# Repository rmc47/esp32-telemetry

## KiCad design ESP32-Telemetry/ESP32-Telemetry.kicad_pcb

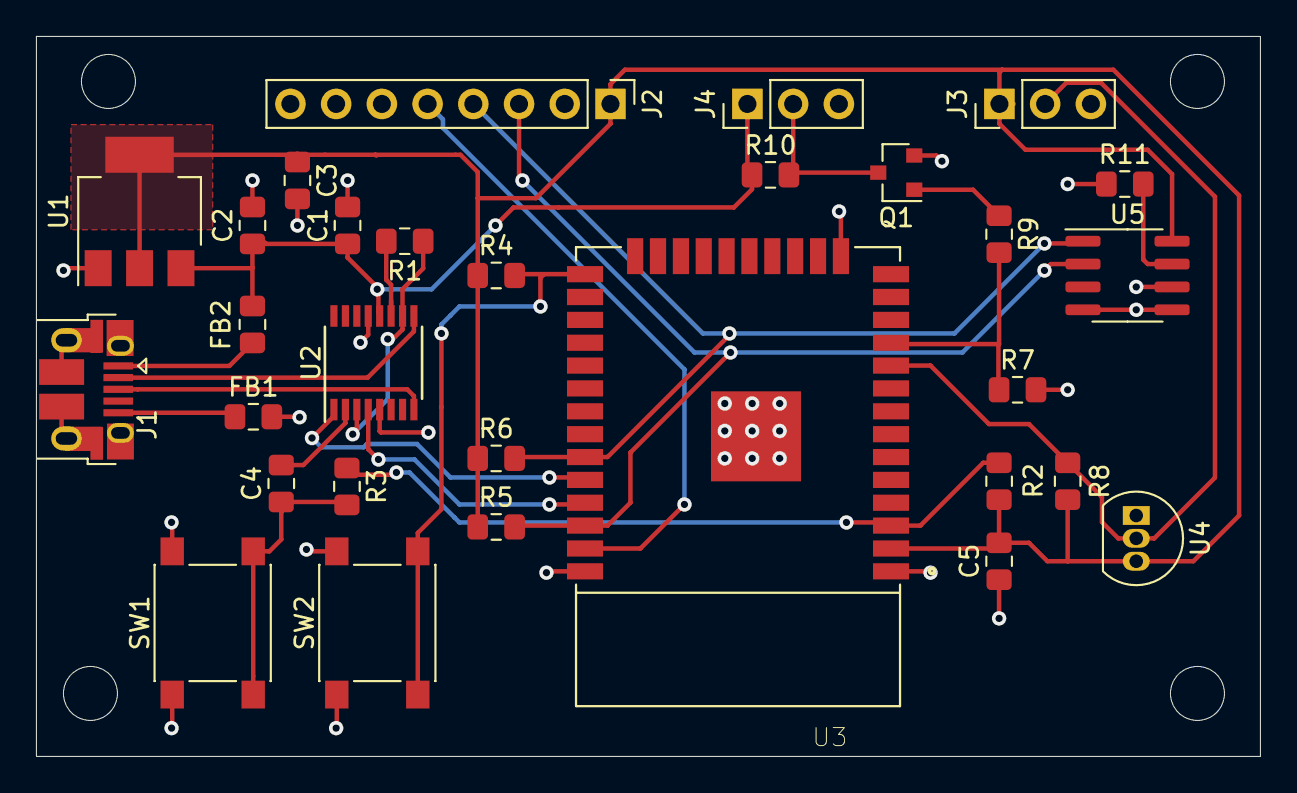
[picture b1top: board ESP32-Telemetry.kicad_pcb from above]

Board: 2 copper layers, 68.0 x 40.0 mm, 30 parts (0 on the bottom side), 23 nets.

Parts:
C1, C5: 100n; C_0805_2012Metric_Pad1.15x1.40mm_HandSolder
C2, C3: 10u; C_0805_2012Metric_Pad1.15x1.40mm_HandSolder
C4: 1u; C_0805_2012Metric_Pad1.15x1.40mm_HandSolder
FB1, FB2: Ferrite_Bead; L_0805_2012Metric_Pad1.15x1.40mm_HandSolder
J1: USB_B_Micro; USB_Micro-B_Amphenol_10103594-0001LF_Horizontal
J2: CJMCU-811; PinHeader_1x08_P2.54mm_Vertical
J3: DS18B20; PinHeader_1x03_P2.54mm_Vertical
J4: LEDs; PinHeader_1x03_P2.54mm_Vertical
Q1: 2N7002; SOT-23
R1, R2, R4, R7, R9, R10: 47k; R_0805_2012Metric_Pad1.15x1.40mm_HandSolder
R3, R11: 0R; R_0805_2012Metric_Pad1.15x1.40mm_HandSolder
R5, R6, R8: 4k7; R_0805_2012Metric_Pad1.15x1.40mm_HandSolder
SW1: Reset; SW_SPST_PTS645
SW2: Prog; SW_SPST_PTS645
U1: NCP1117-3.3_SOT223; SOT-223-3_TabPin2
U2: FT230XS; SSOP-16_3.9x4.9mm_P0.635mm
U3: ESP32-WROOM-32D; MODULE_ESP32-WROOM-32D
U4: DS18B20; TO-92_Inline
U5: LM75B; SOIC-8_3.9x4.9mm_P1.27mm

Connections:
+3V3: C3.1, C5.2, J2.1, J3.1, R2.1, R4.1, R5.1, R6.1, R8.1, U1.2, U3.2, U4.3, U5.8
+5V: C1.1, C2.1, FB2.1, J4.1, R10.1, U1.3, U2.12
/CCS811-Wake: J2.5, U3.37
/DS18B20-Data: J3.2, R8.2, U3.10, U4.2
/LEDs-Data: R7.1, R9.2, U3.11
GND: C1.2, C2.2, C3.2, C5.1, FB1.2, J1.6, J2.2, J3.3, J4.3, Q1.2, R7.2, R11.1, SW1.1, SW2.1, U1.1, U2.5, U2.13, U3.1, U3.15, U3.38, U3.39, U4.1, U5.4, U5.5, U5.6
unnamed: C4.1, R3.2, SW1.2
unnamed: C4.2, U2.2
unnamed: FB1.1, J1.5
unnamed: FB2.2, J1.1
unnamed: J1.2, U2.9
unnamed: J1.3, U2.8
unnamed: J4.2, Q1.3, R10.2
unnamed: Q1.1, R9.1
unnamed: R1.1, U2.3, U2.10
unnamed: R1.2, U2.11
unnamed: R2.2, R3.1, U3.3
unnamed: R4.2, SW2.2, U3.25
unnamed: R11.2, U5.7
unnamed: U2.1, U3.34
unnamed: U2.4, U3.35
SCL: J2.3, R5.2, U3.36, U5.2
SDA: J2.4, R6.2, U3.33, U5.1

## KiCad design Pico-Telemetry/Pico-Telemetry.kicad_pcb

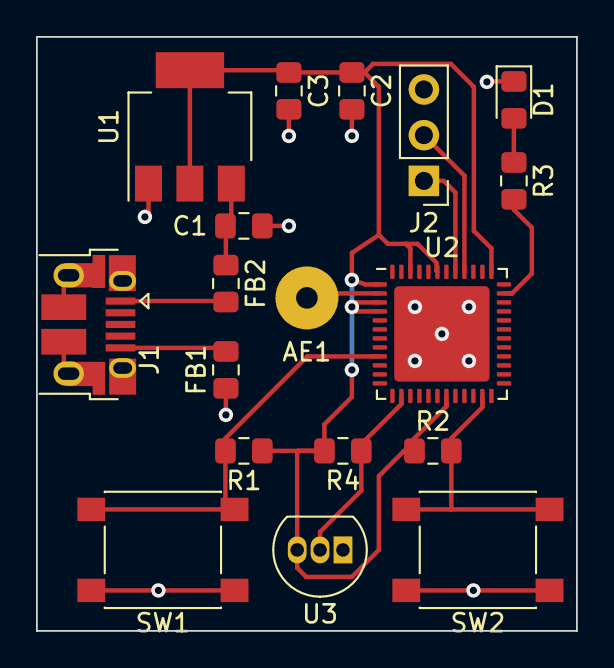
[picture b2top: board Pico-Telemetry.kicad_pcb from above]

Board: 2 copper layers, 30.0 x 33.0 mm, 18 parts (0 on the bottom side), 13 nets.

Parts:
AE1: Antenna; SolderWirePad_1x01_Drill1.2mm
C1, C2: 10u; C_0805_2012Metric_Pad1.15x1.40mm_HandSolder
C3: 100n; C_0805_2012Metric_Pad1.15x1.40mm_HandSolder
D1: LED; LED_0805_2012Metric_Pad1.15x1.40mm_HandSolder
FB1, FB2: Ferrite_Bead; L_0805_2012Metric_Pad1.15x1.40mm_HandSolder
J1: USB_B_Micro; USB_Micro-B_Amphenol_10103594-0001LF_Horizontal
J2: UART; PinHeader_1x03_P2.54mm_Vertical
R1, R2: 47k; R_0805_2012Metric_Pad1.15x1.40mm_HandSolder
R3: 10k; R_0805_2012Metric_Pad1.15x1.40mm_HandSolder
R4: 4k7; R_0805_2012Metric_Pad1.15x1.40mm_HandSolder
SW1: Reset; SW_SPST_PTS645
SW2: Prog; SW_SPST_PTS645
U1: NCP1117-3.3_SOT223; SOT-223-3_TabPin2
U2: ESP32-PICO-D4; QFN-48-1EP_7x7mm_P0.5mm_EP5.3x5.3mm
U3: DS18S20; TO-92_Inline

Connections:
+3V3: C2.1, C3.1, R1.1, R2.1, R4.2, U1.2, U2.1, U2.3, U2.4, U2.19, U2.37, U2.43, U2.46, U3.3
+5V: C1.1, FB2.1, U1.3
GND: C1.2, C2.2, C3.2, D1.1, FB1.1, J1.6, J2.3, SW1.1, SW2.1, U1.1, U2.49, U3.1
unnamed: AE1.1, U2.2
unnamed: D1.2, R3.1
unnamed: FB1.2, J1.5
unnamed: FB2.2, J1.1
unnamed: J2.1, U2.41
unnamed: J2.2, U2.40
unnamed: R1.2, SW1.2, U2.9
unnamed: R2.2, SW2.2, U2.23
unnamed: R3.2, U2.35
unnamed: R4.1, U2.14, U3.2

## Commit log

2020-02-04 Title/name
2020-02-04 Annotated with footprints
2020-02-04 Netlist and initial import to pcbnew
2020-02-04 Starting on PCB layout...
2020-02-04 First shot at layout...
2020-02-04 Missed a ground on Q1
2020-02-04 WIP layout. Bit of a 🚮🔥 at the moment.
2020-02-05 Forgot the USB termination resistors
2020-02-06 Add some order codes
2020-02-17 Wafer-thin pico version
2020-02-19 As submitted 2020-02-15
2020-02-19 WIP routing
